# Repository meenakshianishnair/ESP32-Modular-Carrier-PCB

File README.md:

# ESP32 Modular Carrier PCB

## Overview
A custom-designed 80 mm x 96 mm carrier board built in KiCad to host an ESP32 DevKitC along with modular peripheral connections for an I2C OLED display, Time-of-Flight (ToF) sensor, capacitive touch input, and dedicated 5V power input.

## Specifications
- **Board Dimensions:** 80.0 mm x 96.0 mm
- **Copper Layers:** 2-layer (F.Cu for routing, B.Cu / GND plane)
- **Design Rules:** Zero DRC errors, 0.25 mm track width, standard 2.54 mm pin spacing.

## Bill of Materials (BOM)
| Item | Qty | Reference | Footprint | Description |
| :--- | :--- | :--- | :--- | :--- |
| **1** | 1 | `U1` | Module_ESP32_DevKitC | ESP32 DevKitC Development Board (Socket headers) |
| **2** | 1 | `OLED` | PinHeader_1x04_P2.54mm_Vertical | 0.96" I2C OLED Display Module (4-pin) |
| **3** | 1 | `TOF` | PinHeader_1x04_P2.54mm_Vertical | VL53L0X / VL53L1X Time-of-Flight Sensor (4-pin) |
| **4** | 1 | `TOUCH` | PinHeader_1x04_P2.54mm_Vertical | Capacitive Touch Sensor Module (3-pin) |
| **5** | 1 | `PWR` | PinHeader_1x02_P2.54mm_Vertical | 5V / GND Power Input Terminal (2-pin) |

## Assembly Instructions
1. Solder the 19-pin female header sockets onto the central `J_LEFT` and `J_RIGHT` positions to securely mount the ESP32 DevKitC.
2. Solder vertical 2.54mm pin headers for the OLED, ToF, Touch, and Power modules according to their designated silk screen labels.
3. Verify continuity between the 5V and GND input rails before powering on the board.

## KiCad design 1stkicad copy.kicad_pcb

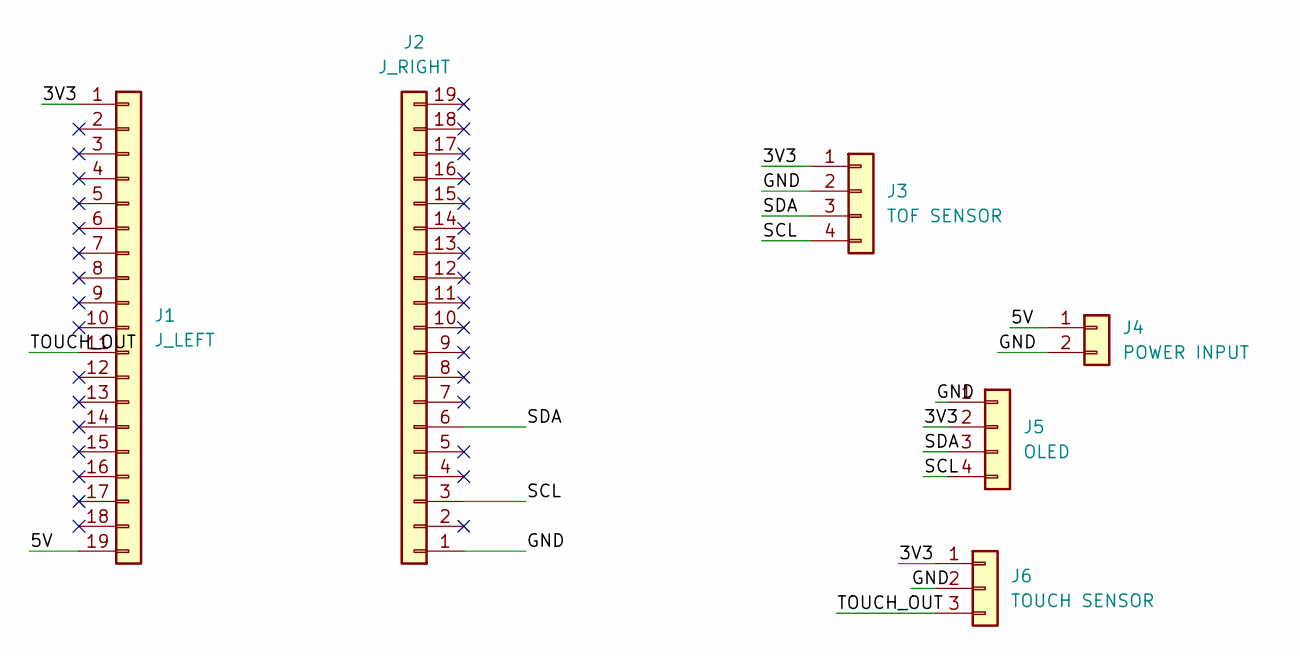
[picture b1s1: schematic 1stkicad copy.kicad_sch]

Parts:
J1: J_LEFT; PinHeader_1x19_P2.54mm_Vertical
J2: J_RIGHT; PinHeader_1x19_P2.54mm_Vertical
J3: TOF SENSOR; PinHeader_1x04_P2.54mm_Vertical
J4: POWER INPUT; PinHeader_1x02_P2.54mm_Vertical
J5: OLED; PinHeader_1x04_P2.54mm_Vertical
J6: TOUCH SENSOR; PinHeader_1x03_P2.54mm_Vertical

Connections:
/3V3: J1.1, J3.1, J5.2, J6.1
/5V: J1.19, J4.1
/GND: J2.1, J3.2, J4.2, J5.1, J6.2
/SCL: J2.3, J3.4, J5.4
/SDA: J2.6, J3.3, J5.3
/TOUCH_OUT: J1.11, J6.3

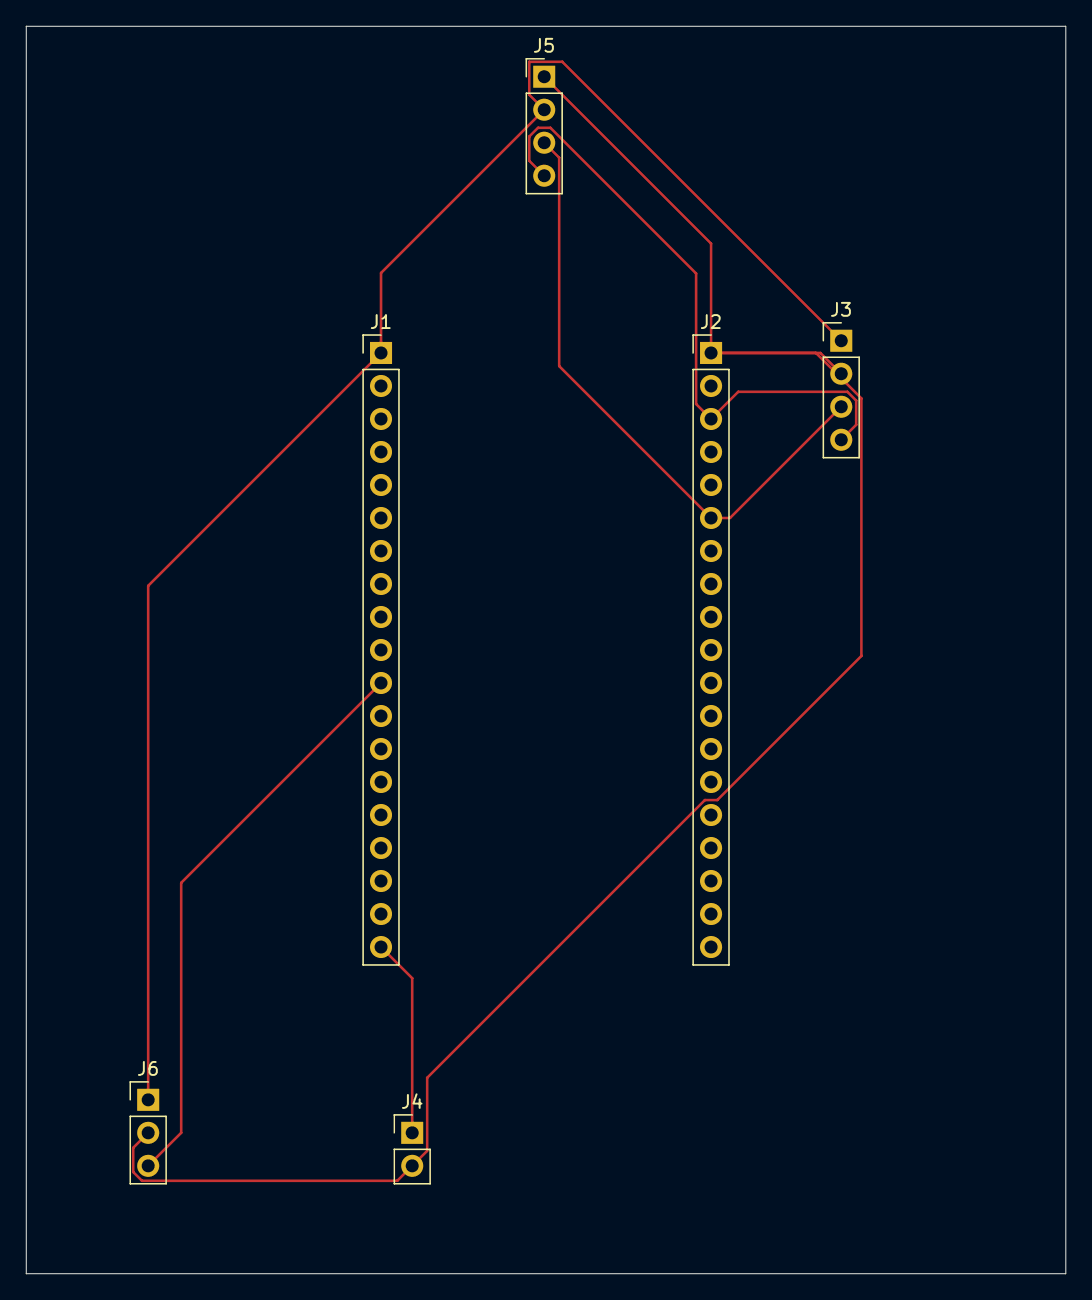
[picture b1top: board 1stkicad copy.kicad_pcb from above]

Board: 2 copper layers, 80.0 x 96.0 mm, 6 parts (0 on the bottom side), 6 nets.

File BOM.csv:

Reference,Qty,Value,Footprint
J1,1,J_LEFT,Connector_PinHeader_2.54mm:PinHeader_1x19_P2.54mm_Vertical
J2,1,J_RIGHT,Connector_PinHeader_2.54mm:PinHeader_1x19_P2.54mm_Vertical
J3,1,TOF SENSOR,Connector_PinHeader_2.54mm:PinHeader_1x04_P2.54mm_Vertical
J4,1,POWER INPUT,Connector_PinHeader_2.54mm:PinHeader_1x02_P2.54mm_Vertical
J5,1,OLED,Connector_PinHeader_2.54mm:PinHeader_1x04_P2.54mm_Vertical
J6,1,TOUCH SENSOR,Connector_PinHeader_2.54mm:PinHeader_1x03_P2.54mm_Vertical
